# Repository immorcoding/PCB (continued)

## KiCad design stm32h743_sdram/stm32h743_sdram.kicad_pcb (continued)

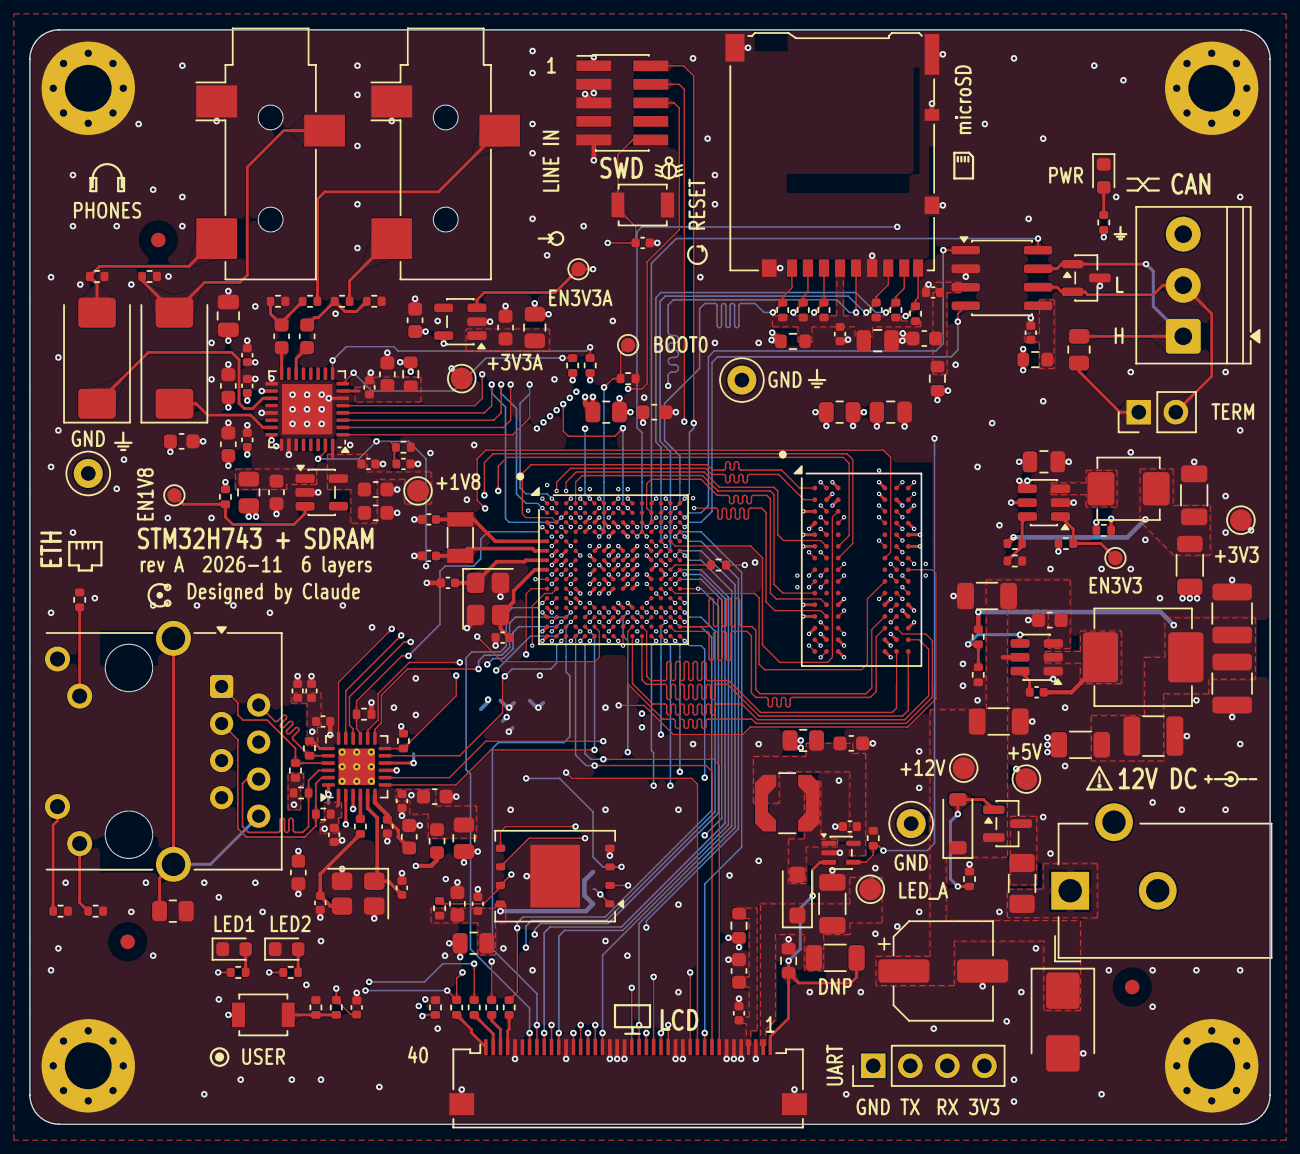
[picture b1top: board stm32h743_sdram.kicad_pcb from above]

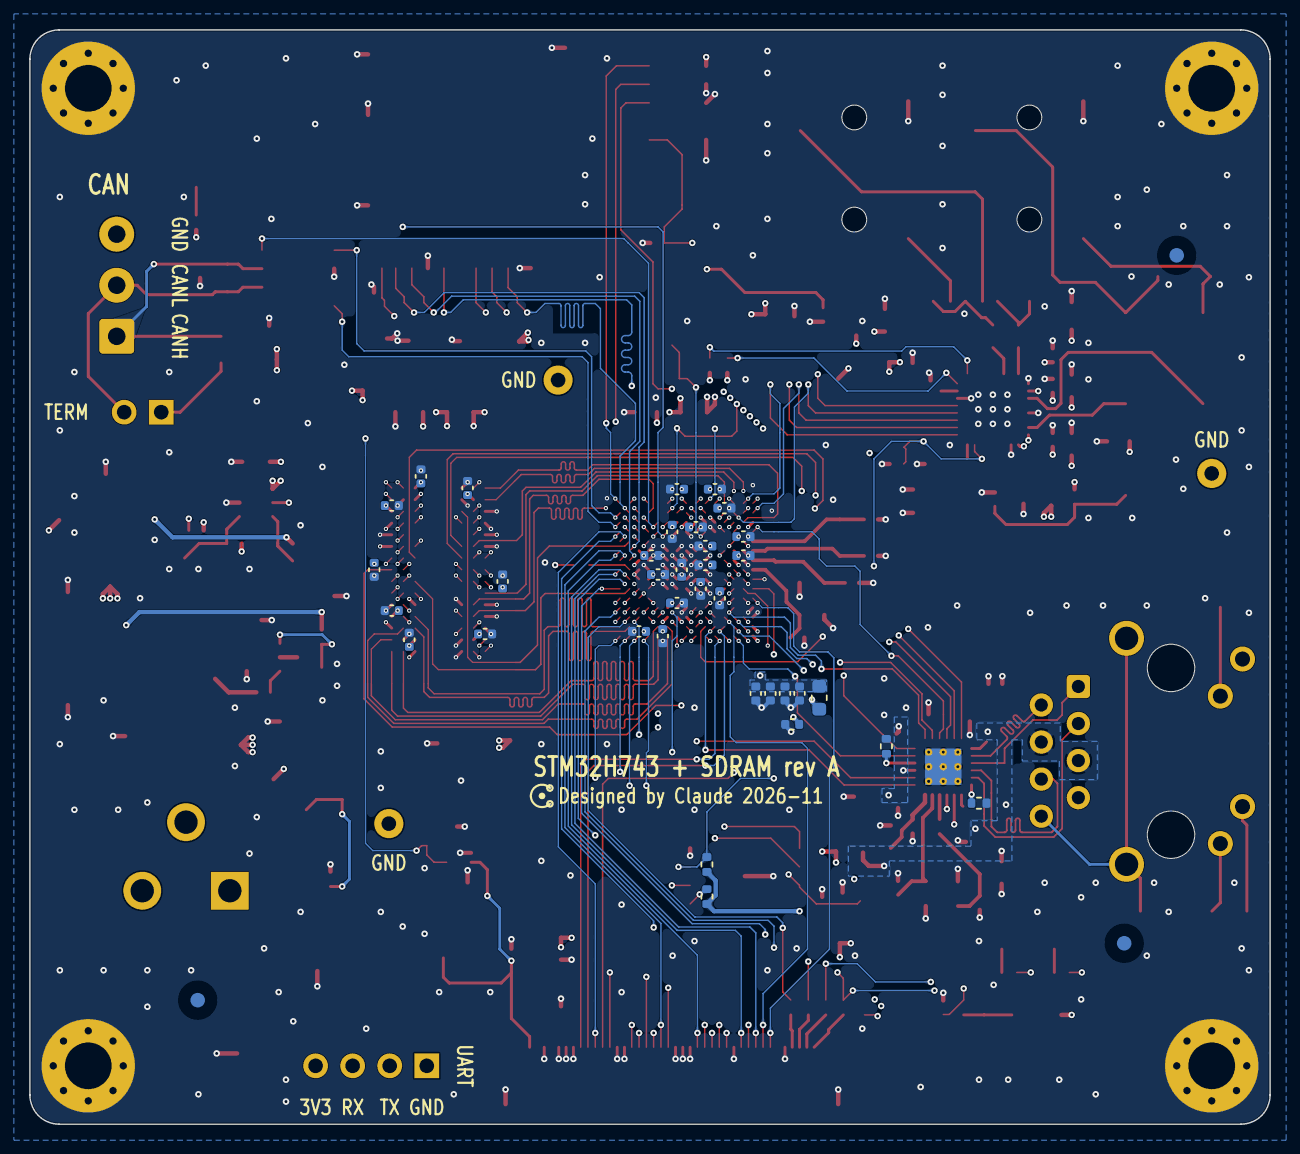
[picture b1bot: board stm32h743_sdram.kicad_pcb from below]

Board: 6 copper layers, 85.0 x 75.0 mm, 223 parts (38 on the bottom side), 204 nets.

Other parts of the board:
FID1, FID2, FID3, FID4, FID5, FID6: Fiducial; Fiducial_1mm_Mask2mm

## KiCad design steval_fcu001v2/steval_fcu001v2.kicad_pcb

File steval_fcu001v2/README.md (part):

# steval_fcu001v2

四层板 layout 测试：ST 官方评估板 STEVAL-FCU001V2（小四轴飞控）的原理图重新录入，加一块自己画的 40 × 40 mm 四层板。

- 原理图来源：`ref/steval-fcu001v2-schematic.pdf`（ST schematic pack Rev 2，2024-06），同目录有 BOM、data brief、UM2958。位号沿用 ST 的。
- 板子：嘉立创四层 JLC04161H-3313，1.6 mm，40 × 40 mm，四角 M3 孔。器件全在顶层，只有第二组电机焊盘在底层。
- 各层用途（2026-11-12 和用户定）：L1 信号和器件，L2 整层地，L3 电源层（`+BATT`，中间一块 `VDD`），L4 信号加铺地。

## 怎么重建

| 步骤 | 命令 |
|---|---|
| 原理图 | `D:\KiCad\bin\python.exe -m Tools.KiCadDesignTools.schematic.build steval_fcu001v2 <输出目录>` |
| 网表进板 | `D:\KiCad\bin\python.exe -m Tools.KiCadDesignTools.schematic.net2pcb <输出目录>\steval_fcu001v2.net steval_fcu001v2\steval_fcu001v2.kicad_pcb` |
| 整板（布局、走线、丝印、泪滴、DRC） | `sh steval_fcu001v2/build_pcb.sh <报告目录>` |

`route.py` 里是手工走线（按区域分函数）和铺铜；自动布线的 21 个网络存在 `auto_tracks.json` 里，由 `route.py` 回放。`auto_tracks.json` 已经用 `Tools/KiCadDesignTools/third_party/auto_tidy.py` 拉直过（过孔和分叉点不动，自动走线从最初的 387 段减到 217 段）；布线器绕远的路径没有改。重跑自动布线的做法见 `CLAUDE.md` 的"走线"一节。

## 审查清单

### 图

- `render_top.png`、`render_bottom.png`：3D 渲染。U1（蓝牙模块）官方库没有 3D 模型，图上只有丝印框。
- `routed.png`：走线示意图。
- 在 KiCad 里看：如果工程开着，先"文件 → 还原"重新载入。

### DRC（`analysis/drc.rpt`，带 `--schematic-parity`）

未连接 0。违规 22 条，逐条说明：

| 类型 | 数量 | 说明 |
|---|---|---|
| `track_angle` | 2（同一处报两次） | B.Cu 上 `MOTOR4` 在 (9.2, 11.7) 有一个 T 型抽头，接到不贴的 R19。是自动布线留下的；试过两种改法（改到过孔处），都会撞上旁边的 NRST，保留 |
| `starved_thermal` | 1 | P3 第 4 脚（GND 插针）在 F.Cu 铺铜上只有 1 根辐条。这个脚在 L2 地平面和 B.Cu 上辐条完整，不影响连接 |
| `silk_edge_clearance` | 5 | BT1（弯针伸出板边）和 CN1（USB 座伸出板边）的封装丝印越过板边，器件本来就悬出 |
| `silk_overlap` | 5 | LD1/LD2 两排 LED 的封装丝印框相碰（排距 1.6 mm），LD3 和 U4 的丝印相碰 |
| `lib_footprint_mismatch` | 9 | U7、U8、Q1–Q4 打开了"允许阻焊桥"，和库里的封装不一样了，原因见下面"规则改动"；P3、P6、P7 删掉了封装自带的丝印外框，原因见"丝印" |

封装一致性 102 条，全部是 `footprint_symbol_field_mismatch`（封装里没有符号的 `ki_keywords` 等字段，`net2pcb.py` 不复制这些字段），没有网络或焊盘不一致。

金丝雀：`OK`。

### 走线约定守得怎么样

| 约定 | 结果 |
|---|---|
| L2 整层地、L3 只做电源面 | 守住。L2、L3 上没有走线 |
| 晶振只走 L1、不打孔，下方 L4 不走线 | 守住。`OSC_IN` 8.2 mm、`OSC_OUT` 5.5 mm，B.Cu 上有禁布区 `XTAL_KEEPOUT` |
| USB 差分只走 L1，0.15/0.15 mm，对内差 ≤ 0.5 mm | 守住。MCU 侧 D+ 15.99 mm、D− 15.92 mm，差 0.07 mm。D+ 上有两个圆弧蛇形（半径 0.25 mm，摆幅 0.5 mm）用来补长。在 U3 处两根线绕开中间的地焊盘，分开 0.77 mm、长约 1.4 mm |
| 电机大电流走短粗线 | 守住。漏极到焊盘 1.0 mm / 0.8 mm 线宽，每个焊盘 3 个过孔连上下层；`+BATT` 走 L3 铜面 |
| 过孔 0.6 / 0.3 mm | **没守住**。MCU 引脚扇出等处用了 23 个 0.45 / 0.2 mm 过孔，其余 169 个是 0.6 / 0.3 |
| 信号线 0.2 mm | 大部分守住。834 mm 走线里 115 mm 是 0.15 mm：USB 差分、MCU 引脚到过孔的短线、蓝牙 SPI 五根线全程 |
| 不做盘中孔 | 两类例外：电机焊盘里的过孔（本来就是为了连上下层），复位键左侧接地焊盘里一个 0.45 mm 过孔（这个焊盘被 NRST、MOTOR3 和 LED 过孔围死）。另有 4 个过孔贴着同网络焊盘的边（C5.1、C19.1、C21.2、D5.2） |
| L4 少走信号 | 25 个网络上了 B.Cu，共 283 mm（F.Cu 是 551 mm）。MCU 四边的信号大多要换层才能出去 |

### 丝印（`silk.py`）

- **位号不上丝印**。按规则的最小字高 0.8 mm，102 个位号只有 55 个能找到不压焊盘的位置，所以一个都不印；位号仍在 F.Fab / B.Fab（AD 的 Assembly 层）上，装配图和贴片坐标不受影响。
- **只印功能标注**，字高 0.8 mm、字宽 0.6 mm、线宽 0.15 mm（`docs/design-rules.md` 的下限，没有再小）。共 52 条：正面 24 条、底面 20 条、电机焊盘正反各 4 条。
- **排针**：P3（I2C）、P6（TIM2）、P7（UART）是直插件，正反两面都标。底面每个引脚都有名字。正面 P7 和 P3 每个引脚都有名字（P3 的竖排在两排针之间）；P6 正面只标了两端的 `+` 和 `G`，中间四个引脚（TIM2 CH1–CH4，从 `+` 往 `G` 依次排）没有位置：排针塑料体到板边只剩 0.6 mm，和 P3 之间的空隙给了 P3 的引脚名。
- 为了放下引脚名，P3、P6、P7 封装自带的丝印外框删掉了，1 脚看方焊盘。
- 其余：`BAT` 和 `+`/`-`、`Mn+`（电机正极焊盘，另一个是负极）、`SWD`、`DIO`/`CLK`（TP1/TP2）、`RST`（按键和 TP3）、`CHG`（充电指示灯）、板名。LD1/LD2 两个用户灯没有标。
- **署名**（应用户要求）：底面蓝牙模块旁有一个四旋翼俯视图的小标志（4.5 mm 见方，自己画的）和三行字 `designed by` / `Claude` / `Fable 5.2 2026`，只在丝印层，压在走线和盖油过孔上，不压焊盘。

### 走线形状（`Tools/KiCadDesignTools/analysis/track_shape.py`，DRC 不查的部分）

2026-11-12 用户审查后返工过一轮，之后的结果：

| 项目 | 数量 | 说明 |
|---|---|---|
| 不在 0°/45°/90° 上的线段 | 0 | |
| 阶梯线（一串微小线段拼成的非 45° 斜线） | 0 | 返工前 `MOTOR1` 上有一段 22 级、2.6 mm 长、整体 78.5° 的阶梯 |
| 2 mm 内 3 个以上折弯 | 12 | 返工前 29 处。11 处在自动走线上，1 处是手工重走的 `MOTOR3` 绕按键焊盘的那一段（3 个折弯共 1.99 mm）。自动走线上的是两端过孔位置固定、中间要绕开焊盘或过孔造成的：`BLE_IRQ`、`LED1`、`LPS22HH_CS`、`MOTOR2`、`MOTOR3`（3 处）、`MOTOR4`、`NRST`（2 处）、`SWCLK`、`USB_MONITOR`、`VBAT_SENSE` |
| 短于 0.1 mm 的线段 | 0 | 返工前 32 个。现在由 DRC 规则 `min_segment` 兜底 |
| 小倒角直角（短于 0.35 mm 的线段两侧合计转 90°） | 0 | 2026-11-13 用户发现 `MOTOR3` 在 U2.45 下方有一处：两个 45° 拐点之间只隔 0.05 mm，相邻角度检查不报。同类共 4 处（`MOTOR3` 两处、`MOTOR1`、`S2_CLK`），都已重走；`MOTOR3` 从引脚直线下到自己的过孔，不再绕 `MOTOR2` 的过孔 |
| 圆弧 | 6 | USB D+ 的两个蛇形 |

### 走线过程中改过的规则

都写在 `steval_fcu001v2.kicad_dru` 开头和 `docs/design-rules.md`。

- **过孔下限 0.6/0.3 → 0.45/0.2 mm**：0.5 mm 间距的 QFN 引脚之间放不下 0.6 mm 过孔（相邻走线中心距 0.5 mm，0.6 过孔至少要 0.502 mm）。0.45/0.2 是嘉立创多层板的能力下限，下单时确认是否加价。
- **孔径下限 0.254 → 0.2、上限 3.048 → 3.3 mm**：前者配合小过孔，后者是 3.2 mm 安装孔。
- **`usb2_skew` 加 `within_diff_pairs`**：原写法把 MCU 侧的差分对（16 mm）和连接器侧的（2 mm）互相比较。
- **`usb2_gap` 上限 0.7 → 0.8 mm**：U3 处绕地焊盘分开的那一段是 0.77 mm。
- **网络类通配符**：`?` 和 `[+-]` 在 KiCad 的网络类匹配里不生效，改成逐个网络名。
- **U7、U8、Q1–Q4 允许阻焊桥**：0.5 mm 间距 LGA 焊盘和 MOS 管 0.65 mm 间距的源/栅焊盘之间，阻焊桥只有 0.05 mm，低于 0.08 mm 下限，板厂会整组开窗。不打开这个选项会报 28 条 `solder_mask_bridge`。

### 走线过程中改过的布局

- LED 挪了两次：先从 MCU 左侧挪走（挡住 USB 差分在 L1 上唯一的通道），再从 MCU 正下方下移（给引脚扇出过孔让位）。
- 晶振下移 1.35 mm，让 `OSC_OUT` 直线进晶振，不挡 NRST 等引脚出线。
- C5、C7、C11、R22、C10、C14、C15、R30 各挪了 0.3–1 mm，都是为过孔或走线通道让位；C10 转了 180°。
- 充电的阻容一列（R30、C15、C14）上移 1.05 mm，USB 差分才能在它下方横移到 U3。

### kicad-happy 的发现（`analysis/kicad_happy_*.txt`）

| 发现 | 判断 |
|---|---|
| 没有光学定位点（FD-001） | 属实。机贴需要，每面 3 个；手焊打样不需要。板上没留位置，要加得再挤 |
| 15 个信号网络最细 0.15 mm（CC-002） | 属实但无碍：数字信号的引脚逃逸段 |
| 测试点覆盖 3/72（TE-001） | 属实，ST 原设计就只有 3 个 |
| `S2_SDI`/`S2_CLK` 是 I2C、缺上拉（PR-001） | 误报。这是 SPI，符号的引脚名叫 SDA/SCL |
| U4 的 STAT 缺上拉（PU-001） | 误报。STAT 经 LD3 和 R29 接 VBUS |
| `USBLC_VBUS` 没有电源（RS-001） | ST 原图如此：U3 的 VBUS 脚只接一个电容 |
| BOM 没有料号、没有规格书（SS-001、DS-001） | 属实，见"未核对项" |

## 和 ST 图纸不一样的地方

| ST 图纸 | 这里 | 原因 |
|---|---|---|
| `V_USB`、`VBAT+` | `VBUS`、`+BATT` | 用 KiCad 自带电源符号 |
| `USB_DP` / `USB_DM`（MCU 侧） | `USB_D+` / `USB_D-` | KiCad 靠 `+`/`-` 后缀识别差分对 |
| `DP` / `DM`（连接器侧） | `USB_CONN_D+` / `USB_CONN_D-` | 同上 |
| `MOTORn-` | `MOTORn_N` | 避免被当成差分对的负端 |
| R25（0R，接在两种地符号之间） | 去掉，只有一个 `GND` | 四层板有完整地平面 |
| 电机排针 P1 / P4 / P2 / P5（2 针） | 裸焊盘 MP1–MP16（每个电机 `+BATT` 和 `Mn_OUT` 各一个，1.5 × 3 mm；MP1–8 在顶层，MP9–16 在底层同一位置） | 用户要求 |
| CN1 Molex 47590-0001（micro-AB，沉板，板边要开槽） | Molex 47346-0001（micro-B，贴片，直板边） | 不开槽；引脚顺序相反，USB 差分对从 MCU 到座子不用交叉 |
| 没有安装孔 | H1–H4，M3 | 原型板固定用 |
| 栅极、LED 阳极等没有名字的节点 | `Mn_GATE`、`LDn_A`、`Mn_OUT`、`CHG_PROG`、`CHG_STAT`、`USB_SHIELD`、`USBLC_VBUS` | 标号画法需要名字 |

## 符号和封装的替代

官方库里没有的器件，用引脚号相同的符号顶替，Value 写的是 ST 的型号。

| 位号 | ST 型号 | 用的符号 | 用的封装 |
|---|---|---|---|
| U3 | USBULC6-2M6（µQFN 1.45×1.0） | `USBLC6-2P6` | `Texas_USON-6_1x1.45mm_P0.5mm_SMD` |
| U4 | STC4054GR（TSOT23-5） | `MCP73831-2-OT` | `TSOT-23-5` |
| U8 | LSM6DSR（LGA-14） | `LSM6DSL` | `LGA-14_3x2.5mm_P0.5mm_LayoutBorder3x4y` |
| U1 | BLUENRG-M0A | `SPBTLE-RF` | `ST_SPBTLE` |
| Q1–Q4 | STL10N3LLH5（图纸）/ STL6N3LLH6（BOM） | `Q_NMOS_SSSGD` | `VSON-8_3.3x3.3mm_P0.65mm_NexFET` |
| D5 | ESDA7P60-1U1M | `D_Zener` | `ST_QFN-2L_1.6x1.0mm` |

## 未核对项

没有对着规格书核对过的引脚、封装和参数。

1. **Q1–Q4 型号和封装**：ST 图纸写 STL10N3LLH5（8 脚，1–3 源极、4 栅极、5–8 漏极），BOM 写 STL6N3LLH6（PowerFLAT 2×2）。这里按图纸的引脚功能，封装用了 3.3×3.3 的通用 VSON-8，没核对过 ST 的推荐焊盘。
2. **U3 封装**：用了尺寸相同的 TI USON-6 顶替，焊盘编号顺序和尺寸没对过 USBULC6-2M6 规格书。
3. **U1 封装和天线净空**：假定 BLUENRG-M0A 和 SPBTLE-RF 焊盘相同。`ST_SPBTLE` 封装自带 12 × 12 mm 的四层禁布区，布局和走线都避开了；这个尺寸是 SPBTLE-RF 的。蓝牙 SPI 五根线从模块下方（禁布区外）的 L1 走，模块底面是否允许走线没查。
4. **U4 引脚**：按图纸上的引脚号（1 CHRG、2 GND、3 BAT、4 VCC、5 PROG）录入，没对过 STC4054 规格书。
5. **U8 引脚**：LSM6DSR 借用 LSM6DSL 符号，图纸上的引脚号和符号一致，没对过规格书。
6. **S1**：KMR231GLFS 用了带接地脚的 `KMR2xxG` 封装，接地脚接 GND；型号是否带接地脚没查。
7. **D5 极性**：按图纸 1 脚接 VBUS；封装的 1 号焊盘是否是阴极没查。
8. **Y1**：BOM 里晶振的型号没读出来（PDF 表格文字错位），封装暂用 3225 四脚，负载电容 15 pF 沿用图纸。
9. **排针**：BT1 用 2.54 mm 弯针，P3、P7、P6 用直针，P8 用 1.27 mm 2×5 贴片针；BOM 的具体料号没逐个对封装。
10. **阻容封装**：统一 0402（图纸上 R1 标 0805、R26 标 0201，BOM 都是 0402）；R12、R13、R16、R17 按 BOM 用 0603。
11. **原板尺寸和外形**：没查。V1 的 Gerber 是双层板，没有官方四层 layout 可对照。
12. **叠层数据**：3313 半固化片 0.0994 mm / Er 4.1、芯板 1.265 mm 是凭记忆写的，没在嘉立创阻抗计算器上核对。USB 线宽 0.15 / 间距 0.15 mm 是按 IPC-2141 公式估的（约 88 Ω）；这块板的 USB 只有全速。
13. **CN1 板边位置**：板边放在封装原点下方 2.7 mm（外壳焊盘外 0.55 mm），没对过 Molex 47346-0001 图纸上的板边尺寸。
14. **0.45/0.2 mm 过孔的价格档**：是否在嘉立创四层板的免加价范围内没查。
15. **L3 上 `+BATT` 的通流**：L3 的 `+BATT` 是围着 `VDD` 岛的一圈，上边在蓝牙天线禁布区下方只有约 2.6 mm 宽（0.5 oz 铜）。四个电机同时峰值电流时的压降和温升没算。

## ERC

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
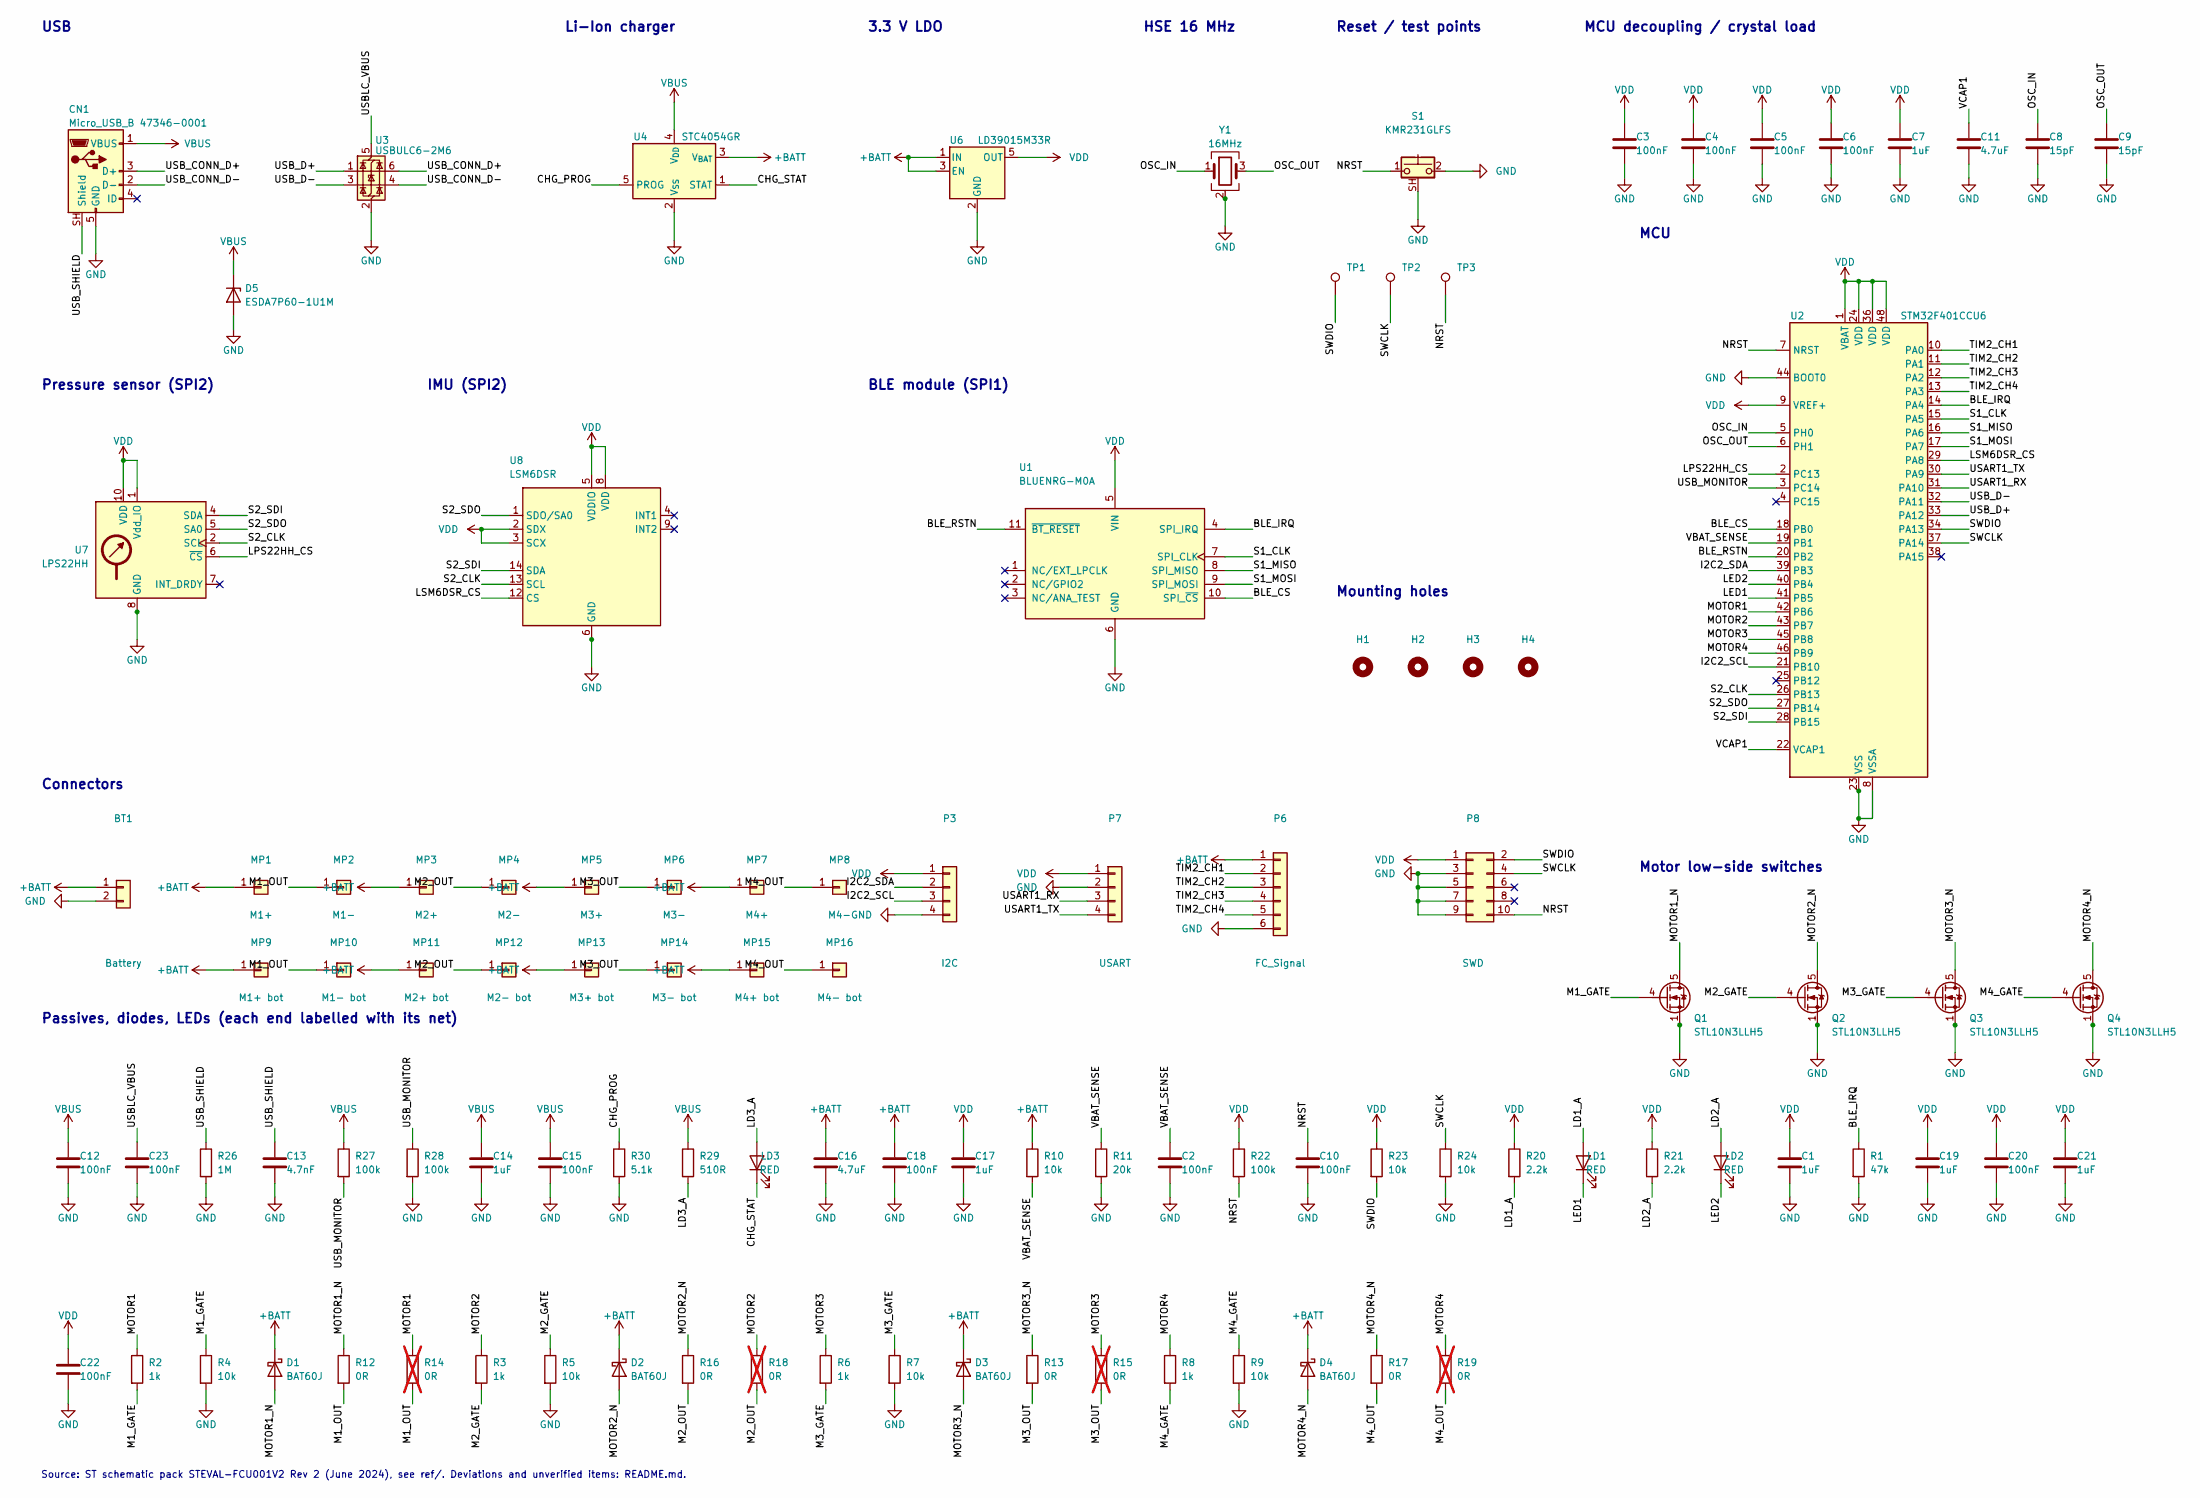
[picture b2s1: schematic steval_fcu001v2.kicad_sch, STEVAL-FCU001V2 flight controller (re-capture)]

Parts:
BT1: Battery; PinHeader_1x02_P2.54mm_Horizontal
C1, C7, C14, C17, C19, C21: 1uF; C_0402_1005Metric
C2, C3, C4, C5, C6, C10, C12, C15, C18, C20, C22, C23: 100nF; C_0402_1005Metric
C8, C9: 15pF; C_0402_1005Metric
C11, C16: 4.7uF; C_0402_1005Metric
C13: 4.7nF; C_0402_1005Metric
CN1: Micro_USB_B 47346-0001; USB_Micro-B_Molex_47346-0001
D1, D2, D3, D4: BAT60J; D_SOD-323
D5: ESDA7P60-1U1M; ST_QFN-2L_1.6x1.0mm
H1, H2, H3, H4: M3; MountingHole_3.2mm_M3
LD1, LD2, LD3: RED; LED_0603_1608Metric
MP1: M1+; SolderWirePad_1x01_SMD_1.5x3mm
MP2: M1-; SolderWirePad_1x01_SMD_1.5x3mm
MP3: M2+; SolderWirePad_1x01_SMD_1.5x3mm
MP4: M2-; SolderWirePad_1x01_SMD_1.5x3mm
MP5: M3+; SolderWirePad_1x01_SMD_1.5x3mm
MP6: M3-; SolderWirePad_1x01_SMD_1.5x3mm
MP7: M4+; SolderWirePad_1x01_SMD_1.5x3mm
MP8: M4-; SolderWirePad_1x01_SMD_1.5x3mm
MP9: M1+ bot; SolderWirePad_1x01_SMD_1.5x3mm
MP10: M1- bot; SolderWirePad_1x01_SMD_1.5x3mm
MP11: M2+ bot; SolderWirePad_1x01_SMD_1.5x3mm
MP12: M2- bot; SolderWirePad_1x01_SMD_1.5x3mm
MP13: M3+ bot; SolderWirePad_1x01_SMD_1.5x3mm
MP14: M3- bot; SolderWirePad_1x01_SMD_1.5x3mm
MP15: M4+ bot; SolderWirePad_1x01_SMD_1.5x3mm
MP16: M4- bot; SolderWirePad_1x01_SMD_1.5x3mm
P3: I2C; PinHeader_1x04_P2.54mm_Vertical
P6: FC_Signal; PinHeader_1x06_P2.54mm_Vertical
P7: USART; PinHeader_1x04_P2.54mm_Vertical
P8: SWD; PinHeader_2x05_P1.27mm_Vertical_SMD
Q1, Q2, Q3, Q4: STL10N3LLH5; VSON-8_3.3x3.3mm_P0.65mm_NexFET
R1: 47k; R_0402_1005Metric
R2, R3, R6, R8: 1k; R_0402_1005Metric
R4, R5, R7, R9, R10, R23, R24: 10k; R_0402_1005Metric
R11: 20k; R_0402_1005Metric
R12, R13, R16, R17: 0R; R_0603_1608Metric
R14, R15, R18, R19: 0R; R_0402_1005Metric; not fitted
R20, R21: 2.2k; R_0402_1005Metric
R22, R27, R28: 100k; R_0402_1005Metric
R26: 1M; R_0402_1005Metric
R29: 510R; R_0402_1005Metric
R30: 5.1k; R_0402_1005Metric
S1: KMR231GLFS; SW_Push_1P1T-SH_NO_CK_KMR2xxG
TP1, TP2, TP3: TP; TestPoint_Pad_D1.0mm
U1: BLUENRG-M0A; ST_SPBTLE
U2: STM32F401CCU6; QFN-48-1EP_7x7mm_P0.5mm_EP5.6x5.6mm
U3: USBULC6-2M6; Texas_USON-6_1x1.45mm_P0.5mm_SMD
U4: STC4054GR; TSOT-23-5
U6: LD39015M33R; SOT-23-5
U7: LPS22HH; ST_HLGA-10_2x2mm_P0.5mm_LayoutBorder3x2y
U8: LSM6DSR; LGA-14_3x2.5mm_P0.5mm_LayoutBorder3x4y
Y1: 16MHz; Crystal_SMD_3225-4Pin_3.2x2.5mm

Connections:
+BATT: BT1.1, C16.1, C18.1, D1.1 (K), D2.1 (K), D3.1 (K), D4.1 (K), MP1.1, MP3.1, MP5.1, MP7.1, MP9.1, MP11.1, MP13.1, MP15.1, P6.1, R10.1, U4.3 (V_{BAT}), U6.1 (IN), U6.3 (EN)
/BLE_CS: U1.10 (SPI_~CS), U2.18 (PB0)
/BLE_IRQ: R1.1, U1.4 (SPI_IRQ), U2.14 (PA4)
/BLE_RSTN: U1.11 (~BT_RESET), U2.20 (PB2)
/CHG_PROG: R30.1, U4.5 (PROG)
/CHG_STAT: LD3.1 (K), U4.1 (STAT)
/I2C2_SCL: P3.3, U2.21 (PB10)
/I2C2_SDA: P3.2, U2.39 (PB3)
/LD1_A: LD1.2 (A), R20.2
/LD2_A: LD2.2 (A), R21.2
/LD3_A: LD3.2 (A), R29.2
/LED1: LD1.1 (K), U2.41 (PB5)
/LED2: LD2.1 (K), U2.40 (PB4)
/LPS22HH_CS: U2.2 (PC13), U7.6 (~CS)
/LSM6DSR_CS: U2.29 (PA8), U8.12 (CS)
/M1_GATE: Q1.4 (G), R2.2, R4.1
/M1_OUT: MP2.1, MP10.1, R12.2, R14.2
/M2_GATE: Q2.4 (G), R3.2, R5.1
/M2_OUT: MP4.1, MP12.1, R16.2, R18.2
/M3_GATE: Q3.4 (G), R6.2, R7.1
/M3_OUT: MP6.1, MP14.1, R13.2, R15.2
/M4_GATE: Q4.4 (G), R8.2, R9.1
/M4_OUT: MP8.1, MP16.1, R17.2, R19.2
/MOTOR1: R2.1, R14.1, U2.42 (PB6)
/MOTOR1_N: D1.2 (A), Q1.5 (D), R12.1
/MOTOR2: R3.1, R18.1, U2.43 (PB7)
/MOTOR2_N: D2.2 (A), Q2.5 (D), R16.1
/MOTOR3: R6.1, R15.1, U2.45 (PB8)
/MOTOR3_N: D3.2 (A), Q3.5 (D), R13.1
/MOTOR4: R8.1, R19.1, U2.46 (PB9)
/MOTOR4_N: D4.2 (A), Q4.5 (D), R17.1
/NRST: C10.1, P8.10, R22.2, S1.1, TP3.1, U2.7 (NRST)
/OSC_IN: C8.1, U2.5 (PH0), Y1.1
/OSC_OUT: C9.1, U2.6 (PH1), Y1.3
/S1_CLK: U1.7 (SPI_CLK), U2.15 (PA5)
/S1_MISO: U1.8 (SPI_MISO), U2.16 (PA6)
/S1_MOSI: U1.9 (SPI_MOSI), U2.17 (PA7)
/S2_CLK: U2.26 (PB13), U7.2 (SCL), U8.13 (SCL)
/S2_SDI: U2.28 (PB15), U7.4 (SDA), U8.14 (SDA)
/S2_SDO: U2.27 (PB14), U7.5 (SA0), U8.1 (SDO/SA0)
/SWCLK: P8.4, R24.1, TP2.1, U2.37 (PA14)
/SWDIO: P8.2, R23.2, TP1.1, U2.34 (PA13)
/TIM2_CH1: P6.2, U2.10 (PA0)
/TIM2_CH2: P6.3, U2.11 (PA1)
/TIM2_CH3: P6.4, U2.12 (PA2)
/TIM2_CH4: P6.5, U2.13 (PA3)
/USART1_RX: P7.3, U2.31 (PA10)
/USART1_TX: P7.4, U2.30 (PA9)
/USBLC_VBUS: C23.1, U3.5 (VBUS)
/USB_CONN_D+: CN1.3 (D+), U3.6 (I/O1)
/USB_CONN_D-: CN1.2 (D-), U3.4 (I/O2)
/USB_D+: U2.33 (PA12), U3.1 (I/O1)
/USB_D-: U2.32 (PA11), U3.3 (I/O2)
/USB_MONITOR: R27.2, R28.1, U2.3 (PC14)
/USB_SHIELD: C13.1, CN1.SH (Shield), R26.1
/VBAT_SENSE: C2.1, R10.2, R11.1, U2.19 (PB1)
/VCAP1: C11.1, U2.22 (VCAP1)
GND: BT1.2, C1.2, C2.2, C3.2, C4.2, C5.2, C6.2, C7.2, C8.2, C9.2, C10.2, C11.2, C12.2, C13.2, C14.2, C15.2, C16.2, C17.2, C18.2, C19.2, C20.2, C21.2, C22.2, C23.2, CN1.5 (GND), D5.2 (A), P3.4, P6.6, P7.2, P8.3, P8.5, P8.7, P8.9, Q1.1 (S), Q1.2 (S), Q1.3 (S), Q2.1 (S), Q2.2 (S), Q2.3 (S), Q3.1 (S), Q3.2 (S), Q3.3 (S), Q4.1 (S), Q4.2 (S), Q4.3 (S), R1.2, R4.2, R5.2, R7.2, R9.2, R11.2, R24.2, R26.2, R28.2, R30.2, S1.2, S1.SH (B), U1.6 (GND), U2.8 (VSSA), U2.23 (VSS), U2.35 (VSS), U2.44 (BOOT0), U2.47 (VSS), U2.49 (VSS), U3.2 (GND), U4.2 (V_{SS}), U6.2 (GND), U7.3 (GND), U7.8 (GND), U7.9 (GND), U8.6 (GND), U8.7 (GND), Y1.2 (G), Y1.4 (G)
VBUS: C12.1, C14.1, C15.1, CN1.1 (VBUS), D5.1 (K), R27.1, R29.1, U4.4 (V_{DD})
VDD: C1.1, C3.1, C4.1, C5.1, C6.1, C7.1, C17.1, C19.1, C20.1, C21.1, C22.1, P3.1, P7.1, P8.1, R20.1, R21.1, R22.1, R23.1, U1.5 (VIN), U2.1 (VBAT), U2.9 (VREF+), U2.24 (VDD), U2.36 (VDD), U2.48 (VDD), U6.5 (OUT), U7.1 (Vdd_IO), U7.10 (VDD), U8.2 (SDX), U8.3 (SCX), U8.5 (VDDIO), U8.8 (VDD)

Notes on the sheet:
Mounting holes
MCU decoupling / crystal load
3.3 V LDO
IMU (SPI2)
Passives, diodes, LEDs (each end labelled with its net)
Motor low-side switches
Li-Ion charger
MCU
Pressure sensor (SPI2)
BLE module (SPI1)
USB
Source: ST schematic pack STEVAL-FCU001V2 Rev 2 (June 2024), see ref/. Deviations and unverified items: README.md.
Connectors
HSE 16 MHz
Reset / test points

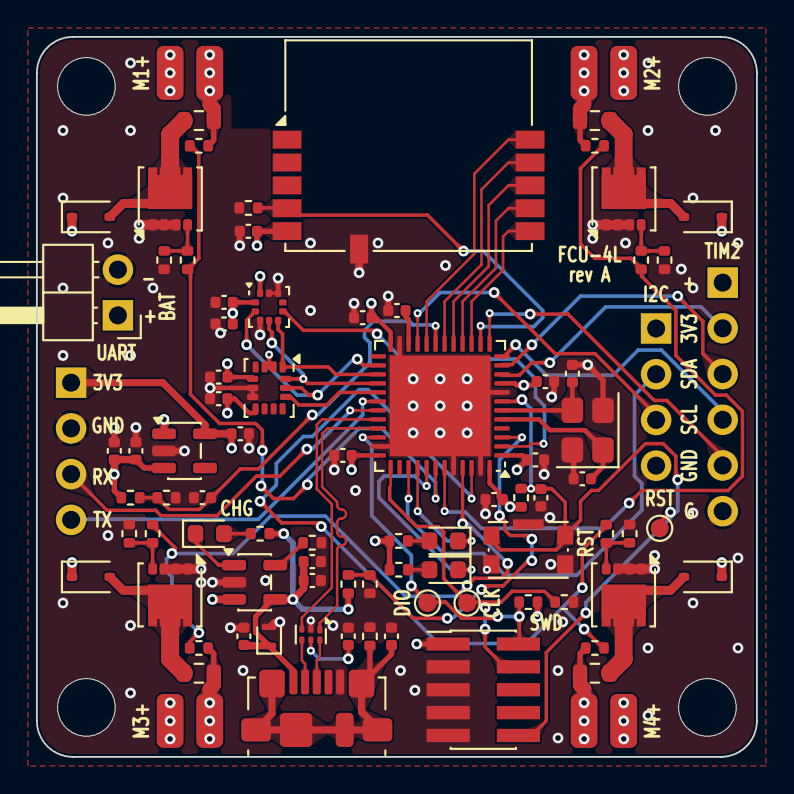
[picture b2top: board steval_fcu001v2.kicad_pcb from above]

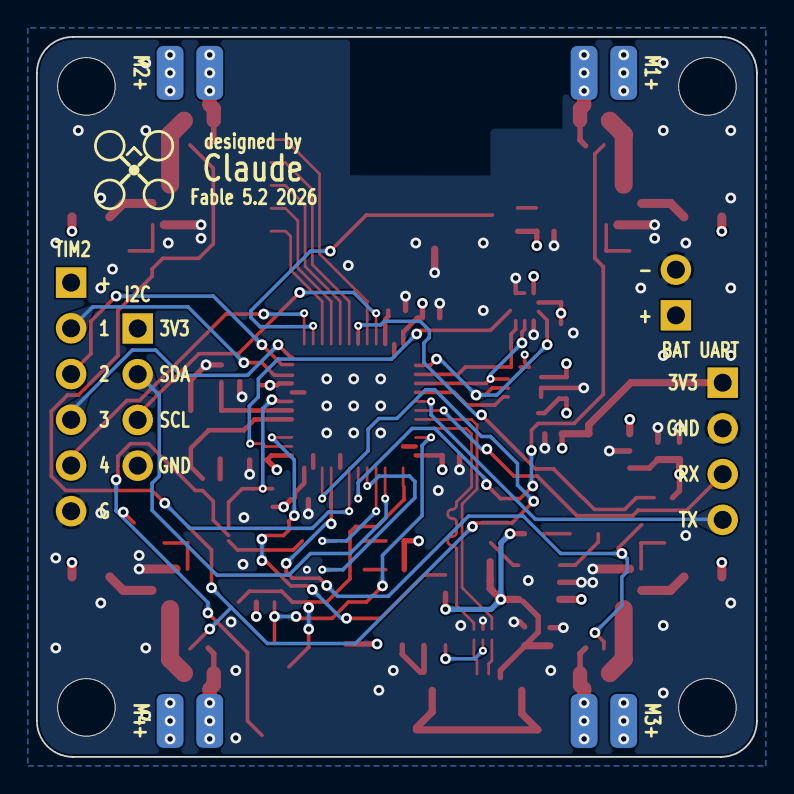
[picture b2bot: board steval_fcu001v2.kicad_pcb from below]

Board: 4 copper layers, 40.0 x 40.0 mm, 102 parts (8 on the bottom side), 60 nets.

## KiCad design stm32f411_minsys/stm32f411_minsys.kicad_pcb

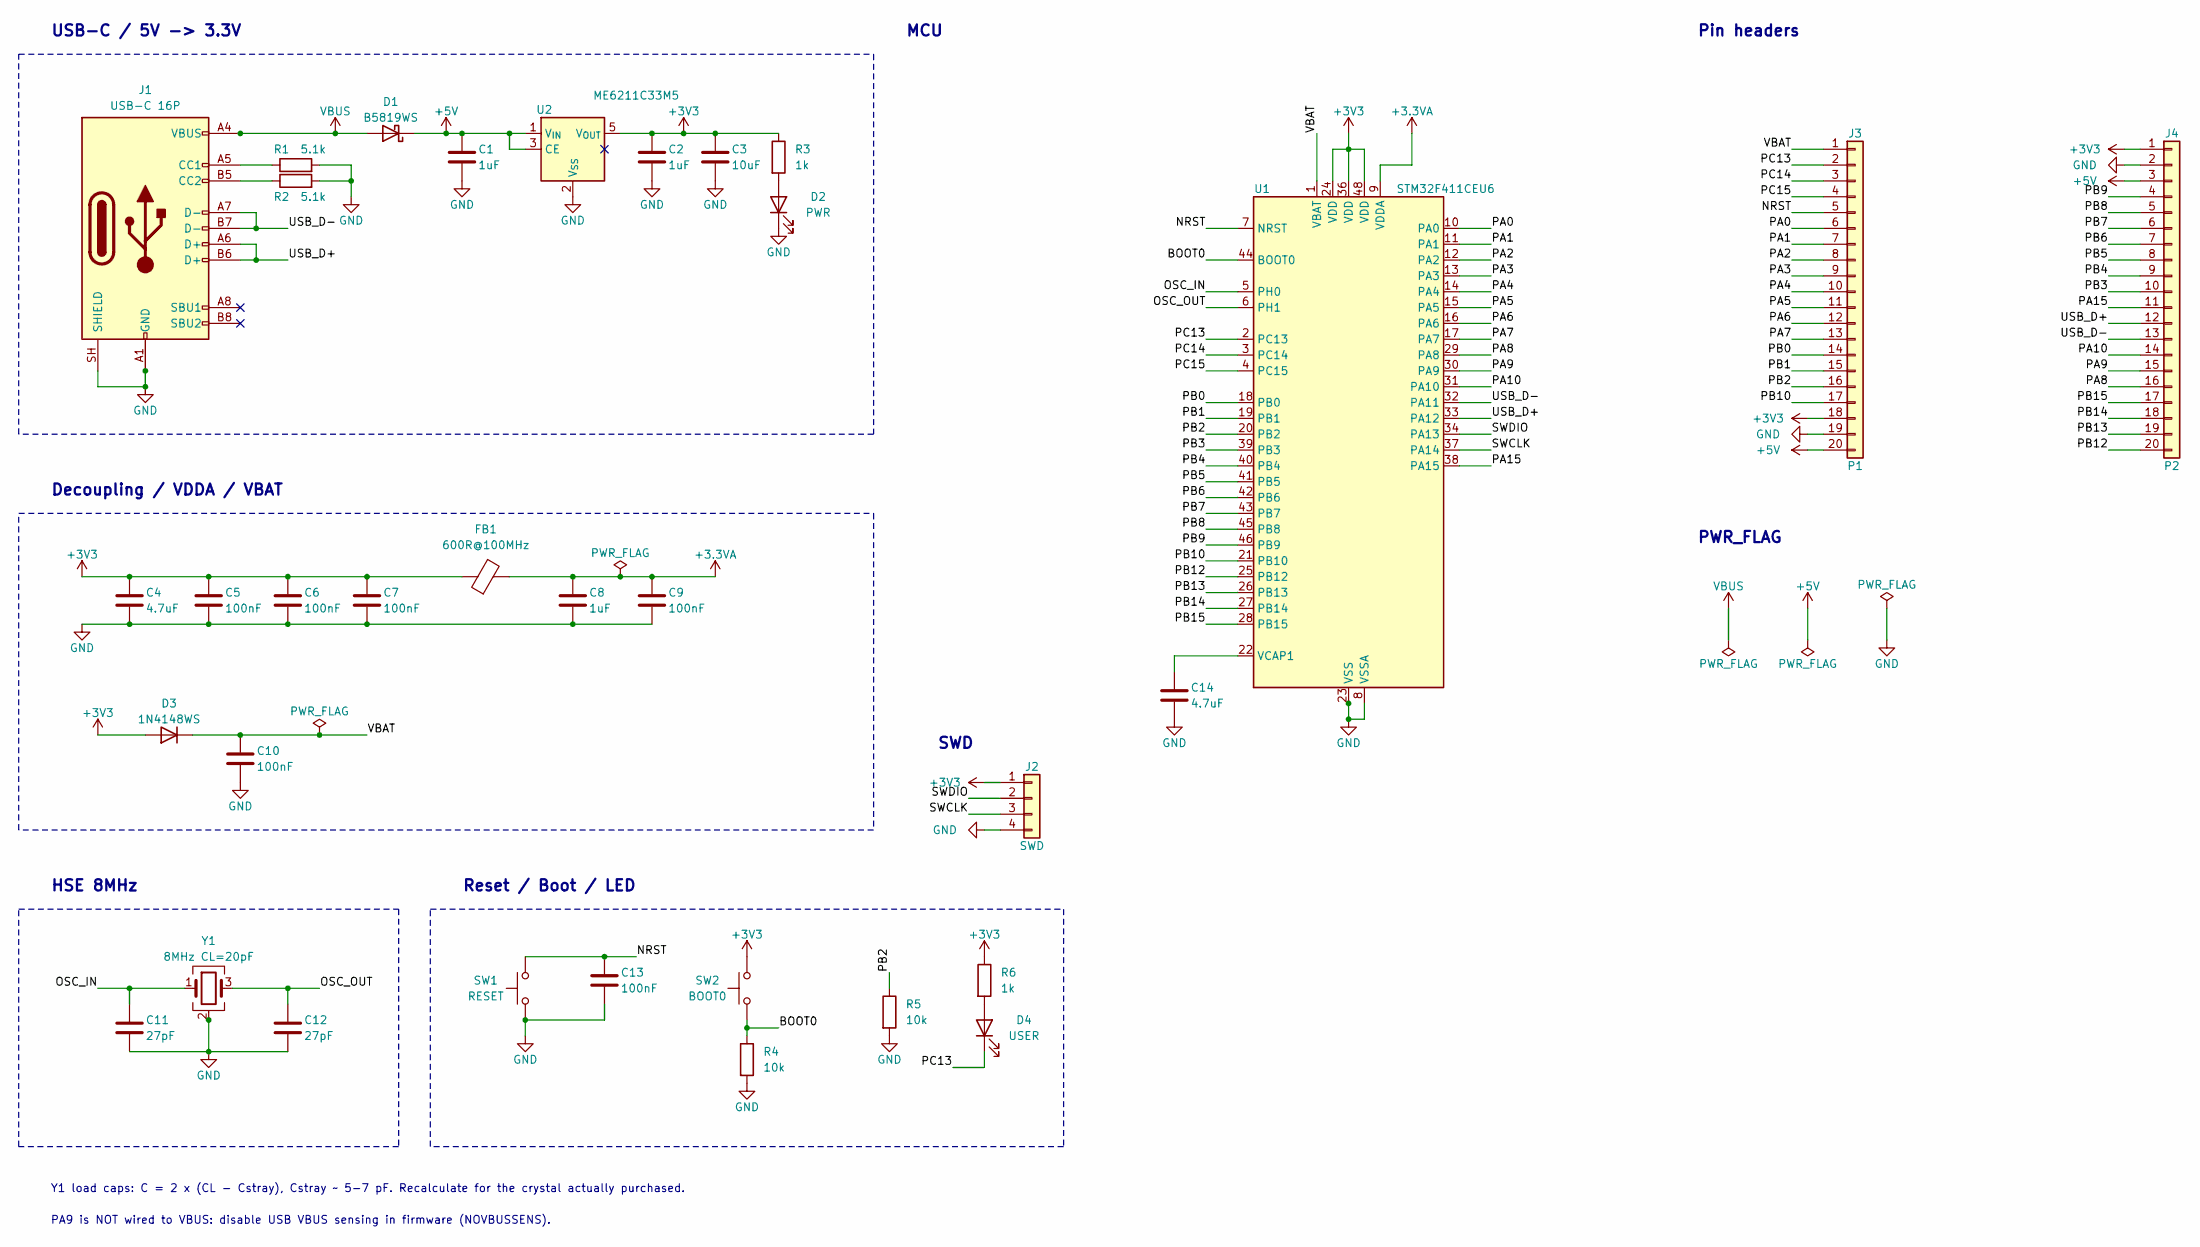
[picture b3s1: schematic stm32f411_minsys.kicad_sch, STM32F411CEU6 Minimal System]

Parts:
C1, C2, C8: 1uF; C_0603_1608Metric
C3: 10uF; C_0603_1608Metric
C4, C14: 4.7uF; C_0603_1608Metric
C5, C6, C7, C9, C10, C13: 100nF; C_0603_1608Metric
C11, C12: 27pF; C_0603_1608Metric
D1: B5819WS; D_SOD-323
D2: PWR; LED_0603_1608Metric
D3: 1N4148WS; D_SOD-323
D4: USER; LED_0603_1608Metric
FB1: 600R@100MHz; L_0603_1608Metric
J1: USB-C 16P; USB_C_Receptacle_HRO_TYPE-C-31-M-12
J2: SWD; PinHeader_1x04_P2.54mm_Horizontal
J3: P1; PinHeader_1x20_P2.54mm_Vertical
J4: P2; PinHeader_1x20_P2.54mm_Vertical
R1, R2: 5.1k; R_0603_1608Metric
R3, R6: 1k; R_0603_1608Metric
R4, R5: 10k; R_0603_1608Metric
SW1: RESET; SW_SPST_TS-1088-xR020
SW2: BOOT0; SW_SPST_TS-1088-xR020
U1: STM32F411CEU6; QFN-48-1EP_7x7mm_P0.5mm_EP5.6x5.6mm
U2: ME6211C33M5; SOT-23-5
Y1: 8MHz CL=20pF; Crystal_SMD_3225-4Pin_3.2x2.5mm

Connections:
+3.3VA: C8.1, C9.1, FB1.2, U1.9 (VDDA)
+3V3: C2.1, C3.1, C4.1, C5.1, C6.1, C7.1, D3.2 (A), FB1.1, J2.1, J3.18, J4.1, R3.1, R6.1, SW2.2, U1.24 (VDD), U1.36 (VDD), U1.48 (VDD), U2.5 (V_{OUT})
+5V: C1.1, D1.1 (K), J3.20, J4.3, U2.1 (V_{IN}), U2.3 (CE)
/BOOT0: R4.1, SW2.1, U1.44 (BOOT0)
/NRST: C13.1, J3.5, SW1.2, U1.7 (NRST)
/OSC_IN: C11.1, U1.5 (PH0), Y1.1
/OSC_OUT: C12.1, U1.6 (PH1), Y1.3
/PA0: J3.6, U1.10 (PA0)
/PA1: J3.7, U1.11 (PA1)
/PA2: J3.8, U1.12 (PA2)
/PA3: J3.9, U1.13 (PA3)
/PA4: J3.10, U1.14 (PA4)
/PA5: J3.11, U1.15 (PA5)
/PA6: J3.12, U1.16 (PA6)
/PA7: J3.13, U1.17 (PA7)
/PA8: J4.16, U1.29 (PA8)
/PA9: J4.15, U1.30 (PA9)
/PA10: J4.14, U1.31 (PA10)
/PA15: J4.11, U1.38 (PA15)
/PB0: J3.14, U1.18 (PB0)
/PB1: J3.15, U1.19 (PB1)
/PB2: J3.16, R5.1, U1.20 (PB2)
/PB3: J4.10, U1.39 (PB3)
/PB4: J4.9, U1.40 (PB4)
/PB5: J4.8, U1.41 (PB5)
/PB6: J4.7, U1.42 (PB6)
/PB7: J4.6, U1.43 (PB7)
/PB8: J4.5, U1.45 (PB8)
/PB9: J4.4, U1.46 (PB9)
/PB10: J3.17, U1.21 (PB10)
/PB12: J4.20, U1.25 (PB12)
/PB13: J4.19, U1.26 (PB13)
/PB14: J4.18, U1.27 (PB14)
/PB15: J4.17, U1.28 (PB15)
/PC13: D4.1 (K), J3.2, U1.2 (PC13)
/PC14: J3.3, U1.3 (PC14)
/PC15: J3.4, U1.4 (PC15)
/SWCLK: J2.3, U1.37 (PA14)
/SWDIO: J2.2, U1.34 (PA13)
/USB_D+: J1.A6 (D+), J1.B6 (D+), J4.12, U1.33 (PA12)
/USB_D-: J1.A7 (D-), J1.B7 (D-), J4.13, U1.32 (PA11)
/VBAT: C10.1, D3.1 (K), J3.1, U1.1 (VBAT)
GND: C1.2, C2.2, C3.2, C4.2, C5.2, C6.2, C7.2, C8.2, C9.2, C10.2, C11.2, C12.2, C13.2, C14.2, D2.1 (K), J1.A1 (GND), J1.A12 (GND), J1.B1 (GND), J1.B12 (GND), J1.SH (SHIELD), J2.4, J3.19, J4.2, R1.2, R2.2, R4.2, R5.2, SW1.1, U1.8 (VSSA), U1.23 (VSS), U1.35 (VSS), U1.47 (VSS), U1.49 (VSS), U2.2 (V_{SS}), Y1.2 (G), Y1.4 (G)
unnamed: D2.2 (A), R3.2
unnamed: D4.2 (A), R6.2
unnamed: J1.A5 (CC1), R1.1
unnamed: J1.B5 (CC2), R2.1
unnamed: C14.1, U1.22 (VCAP1)
VBUS: D1.2 (A), J1.A4 (VBUS), J1.A9 (VBUS), J1.B4 (VBUS), J1.B9 (VBUS)

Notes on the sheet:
PA9 is NOT wired to VBUS: disable USB VBUS sensing in firmware (NOVBUSSENS).
MCU
HSE 8MHz
PWR_FLAG
Reset / Boot / LED
Decoupling / VDDA / VBAT
SWD
Y1 load caps: C = 2 x (CL - Cstray), Cstray ~ 5-7 pF. Recalculate for the crystal actually purchased.
USB-C / 5V -> 3.3V
Pin headers

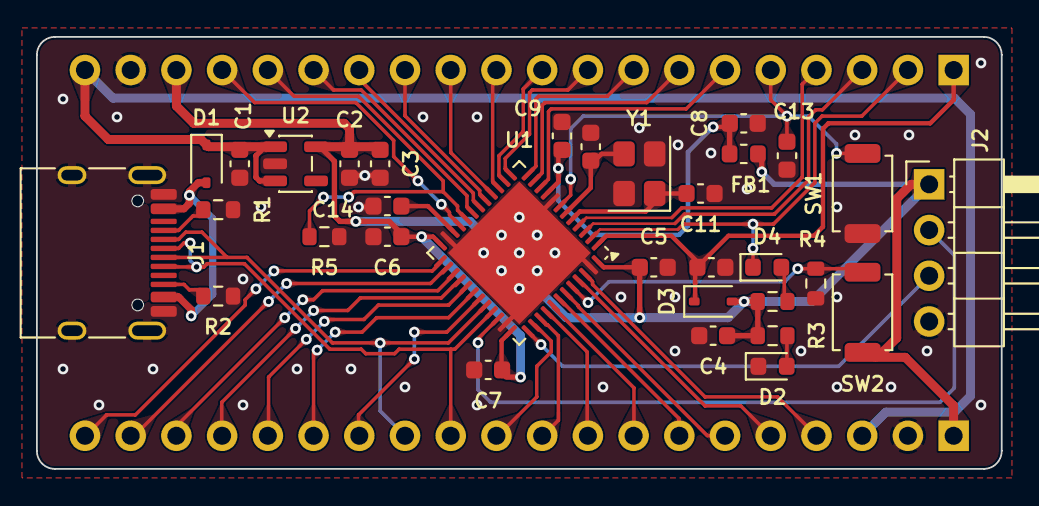
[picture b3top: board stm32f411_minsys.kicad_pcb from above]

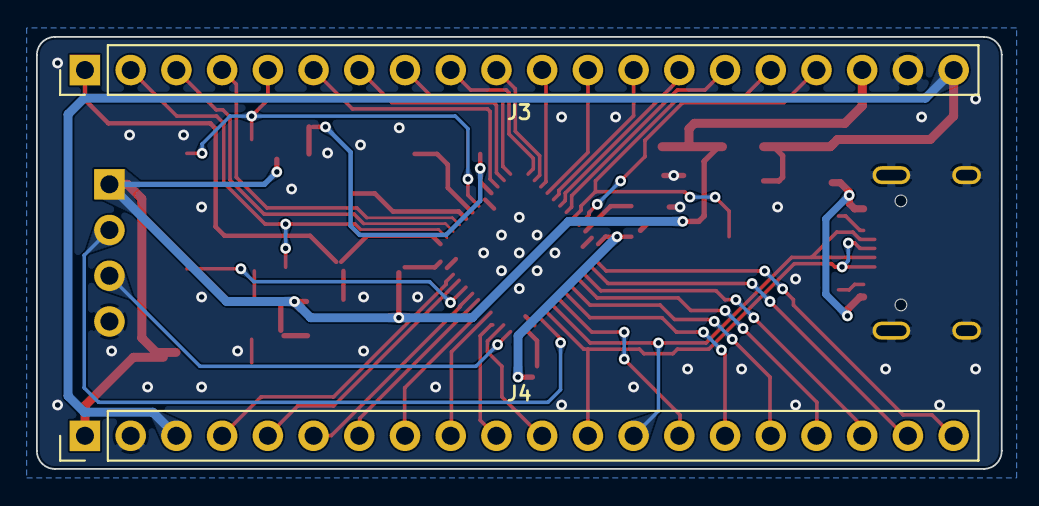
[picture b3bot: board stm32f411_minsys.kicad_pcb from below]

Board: 2 copper layers, 53.6 x 24.0 mm, 34 parts (2 on the bottom side), 49 nets.

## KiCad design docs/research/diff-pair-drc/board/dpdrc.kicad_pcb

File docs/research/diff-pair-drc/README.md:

# 实测：KiCad 10.0.8 的差分对 DRC（E1–E5）

票：[#44](https://github.com/immorcoding/PCB/issues/44)（地图 [#26](https://github.com/immorcoding/PCB/issues/26)）。日期 2026-11-26，KiCad 10.0.8，Windows 11。
分支 `research/diff-pair-drc`，只存档不合并。要核对的说法来自分支 `research/diff-pair-tooling` 的 `docs/research/diff-pair-tooling.md`（下称“调研”）第 3.4 节和第 9 节，那些都是读源码得出的，没有运行过。

## 怎么跑的

```
python docs/research/diff-pair-drc/run.py          # 在仓库根目录，系统 python
```

`run.py` 经 `core.heavy` 一次只跑一个重活：

1. `D:\KiCad\bin\python.exe docs/research/diff-pair-drc/make_board.py board templates/C-bga-065/C-bga-065.kicad_pro`：写夹具板 `board/dpdrc.kicad_pcb`（两层，线宽 0.1，对内中心距 0.25 即间隙 0.15，网络类 Default 只改了线宽、间距 0.1 和差分对参数）和 `board/predict.json`。坐标全部是整数 nm，直接写进 `VECTOR2I`；板文件里保留到 nm（例：`/E1B_N` 从 `7.911612 0.088389` 到 `12.911613 5.088389`）。
2. 每套规则一次：`kicad-cli pcb drc --severity-all --units mm --format json -o results/<套>.json work/<套>/dpdrc.kicad_pcb`，规则文件在 `rules/<套>.kicad_dru`。
3. `results/summary.txt`：每套规则里和差分对有关的报告原文，后面附 `predict.json` 的预测。

结束时没有 KiCad 进程在跑（`heavy.running()` 为空）。

同一套跑了两遍（第二遍只改了预测里圆弧耦合长度的算法），两遍的 94 个报告值逐个相同；报告的顺序和引用的是哪一段不同，因为 pcbnew 每次给对象新的 uuid。

预测是按调研第 3.4 节的读法算的：两段同层、方向向量整数叉积恰为 0、不共线、投影重叠，间隙在窗口内才算耦合；非耦合 = max(P 长, N 长) − Σ耦合重叠长度。**预测不含“两段之间没有别的铜”这一条**，所以 DRC 和预测不一样的地方就指向它。

每个用例是一对独立的网络 `/<用例>_P`、`/<用例>_N`，所有用例在同一块板上。读数的办法：`diff_pair_uncoupled (max 0.0001mm)`，没有报告即非耦合 ≤ 0.0001 mm，有报告就带实际值；`skew`、`length` 同样用极小的上限逼出实际值。

| 规则套 | 内容 |
|---|---|
| rs1_window_unc | `diff_pair_gap (min 0.14mm)(max 0.2mm)` + `diff_pair_uncoupled (max 0.0001mm)` |
| rs2_minonly_unc | `diff_pair_gap (min 0.14mm)`（无上限）+ `diff_pair_uncoupled (max 0.0001mm)` |
| rs3_window_only | 只有间隙窗口 |
| rs4_window_unc_loose | 间隙窗口 + `diff_pair_uncoupled (max 50mm)`（预算不会超） |
| rs5_skew_length | E3、E4 的 `skew (within_diff_pairs)` 和 `length` 探针 |

## 结果

### E1 整数偏移和“平行”的判定

| 用例 | 几何 | 调研的预测 | DRC（rs1、rs2） |
|---|---|---|---|
| E1A | 45°，N = P + 同一整数向量 | 耦合 | 耦合（无报告） |
| E1B | 45°，浮点中线、P/N 各端分别取整，两线方向差 (1, 0) nm | 非耦合 7.0711 | **耦合**（无报告） |
| E1C | 45°，N 末端故意偏 1 nm | 非耦合 7.0711 | **耦合** |
| E1D | 水平 10 mm，N 末端偏 1 nm | 非耦合 10 | **耦合** |
| E1G / E1H | 两个 45° 弯，按角平分线逐点取整 / 整数偏移线求交 | 0.2071 / 0.2071 | 0.2071 / 0.2071 |

调研说“叉积必须恰为 0”不成立。扫一遍偏差找门槛（N 末端横向偏 d，背离 P）：

| 组 | 长度 | 仍耦合的最大偏差 | 开始非耦合 |
|---|---|---|---|
| E1T 水平 | 10 mm | 1000 nm（1.0e-4 rad） | 3000 nm（3e-4 rad） |
| E1U 水平 | 1 mm | 100 nm（1.0e-4 rad） | 300 nm（3e-4 rad） |
| E1V 45° | 7.07 mm | x 偏 300 nm（垂直分量 3.0e-5 rad） | x 偏 1000 nm（1.0e-4 rad） |

门槛是**角度**，约 1e-4 rad（0.006°），和段长无关；正好 1e-4 时一例耦合一例不耦合。取整到 nm 带来的角度误差是 1 nm / 段长：0.1 mm 的段是 1e-5，离门槛差十倍。

E1G、E1H 的 0.2071 是两个 45° 弯的内外线长差：每个 45° 弯损失 S·tan 22.5°（中心距 S = 0.25 时 0.1036 mm）的耦合长度。

### E2 补偿凸起和圆弧

| 用例 | 几何（凸起都在 P 上，基线 10 mm） | 预测 rs1 / rs2 | DRC rs1 | DRC rs2 | 间隙报告（rs1、rs3、rs4） |
|---|---|---|---|---|---|
| E2Z | 直线对照 | 0 / 0 | 0 | 0 | 无 |
| E2A | 矩形向外，竖腿，高 0.3，顶 0.6 | 1.2 / 0.6 | 1.2000 | **1.2000** | **无** |
| E2B | 矩形向内，高 0.02（间隙 0.15→0.13） | 0.64 / 0.64 | 0.6400 | 0.6400 | 0.13 < 最小 0.14 |
| E2C | 梯形向外，45° 腿，高 0.3，顶 0.6 | 1.4485 / 0.8485 | 1.4485 | 0.8485 | 0.45 > 最大 0.2 |
| E2D | 圆角向外（`tune.py` 的形状：r 0.1 四分之一圆弧、腿 0.1、直顶 0.6） | 1.4283 / 0.8283 | 1.4283 | 0.8283 | 0.45 > 最大 0.2 |
| E2E | 半圆向外，r 0.3 | 0.9425 / 0.9425 | 0.9425 | 0.9425 | 无 |
| E2F | 90° 转弯，同心圆弧 r 1.125 / 0.875 | 0.3927 / 0.3927（耦合长度按内弧，见下） | 0.3927 | 0.3927 | 无 |
| E2G | 90° 转弯，P 圆弧、N 两段 45° 倒角 | 1.7671 | 1.7671 | 1.7671 | 无 |

- 顶边是直线、和 N 平行的向外凸起（梯形、圆角）：顶边**算耦合**，间隙 0.45。有间隙上限时报 `diff_pair_gap_out_of_range` 并计入非耦合；没有上限时它算耦合，非耦合反而少。
- 矩形竖腿凸起（E2A）：顶边**根本不算耦合**，有没有上限都一样，也不报间隙。原因见 E5：挡住它的是 P 自己在凸起起点处的基线。
- 向内凸起（E2B）：顶边耦合，间隙变小，低于下限就报错。
- 圆弧只和同心圆弧配对（E2F 耦合，耦合长度按内弧算，非耦合 = 外弧 − 内弧 = θ·S）；圆弧和直线不配对（E2G 整段弧都算非耦合）；半圆凸起（E2E）不报间隙，代价是整段弧长。

### E3 pad-to-die 和焊盘内的折线（rs5）

| 用例 | 几何 | DRC 的 P 长 | DRC 的 skew（N 对 P） |
|---|---|---|---|
| E3A | 两根直线 10 mm，P 起点焊盘 `die_length` 1.0 | 11.0000 | −1.0000 |
| E3B | P 在 0.6 mm 焊盘里折一下：(0,0)→(0.25,−0.25)→(0.5,0)→(10,0)，几何 10.2071 | **10.1434** | −0.1434 |
| E3C | 同样的折线，焊盘 0.3 mm，拐点在盘外 | 10.2071 | −0.2071 |

pad-to-die 计入 `length` 和 `skew`；焊盘里的那段按“中心到出盘点的直线”折算（E3B：中心到 (0.3, −0.2) 0.3606 + 0.2828 + 9.5 = 10.1434），和调研第 3.2 节、K53 一致。

### E4 `skew (within_diff_pairs)` 只命中一根网络（rs5）

| 用例 | 规则条件 | 长度（`length` 探针） | skew 报告 |
|---|---|---|---|
| E4A | `A.NetName == '/E4A_P'` | P 10.0000，N 11.0000 | **无**（静默跳过） |
| E4B | `A.inDiffPair('/E4B')`（对照） | 同上 | −1.0000 |
| E4C | 只有 `/E4C_P`，板上没有 `/E4C_N` | P 10.0000 | 无 |

### E5 成对换层、两线之间的铜

| 用例 | 几何 | 预测 | DRC rs1 | DRC rs2 |
|---|---|---|---|---|
| E5A | F 层成对线 45° 张开到过孔对（中心距 0.7），B 层收回；两个 GND 过孔在外侧 | 0.6364 | 0.6364 | 0.6364 |
| E5D | 宽对（间隙 0.75），中间无过孔（对照） | — / 0 | 10（间隙越界） | 0 |
| E5C | 宽对，GND 过孔在两线中间 x = 5 | — / 0 | 10 | **0** |
| E5E / E5F | 宽对，GND 过孔在 x = 0.3 / 9.7（过孔不压到端点） | — / 0 | 10 | **0** |
| E5G | 宽对，GND 过孔圆心在 x = 0（重叠段起点） | — / 0 | 10 | **10.0000** |
| E5H | 宽对，GND 过孔圆心在 x = 10（重叠段终点） | — / 0 | 10 | **0** |

- 过孔不计长度；张开段不平行，全算非耦合（E5A 正好是两段张开线 2 × 0.3182）；不同层上碰巧平行的两段不配对。
- “两段之间有没有别的铜”只在**重叠段的一端**查一条横线（这里是起点 x = 0）：中间、靠近两端但不压线的过孔都不挡；压在起点的过孔让整段 10 mm 不算耦合。E2A 的矩形凸起就是这样被 P 自己的基线挡掉的。两根线方向相反时查哪一端，没有测。

### 报告规则（rs3、rs4 对 rs1）

- 间隙越界**总是报**：rs3（无非耦合规则）和 rs4（非耦合预算 50 mm 没超）都报同样的 8 条。调研第 3.4 节“同时写两条规则、预算没超就不报间隙”不成立。
- 非耦合也超限时（rs1、rs2），每条间隙越界在报告里**出现两次**（rs1 共 16 条 = 2 × 8）。

## 对调研的更正

1. 第 0 节第 3 条、第 3.4 节“必须恰为 0”：实际门槛是约 1e-4 rad 的角度，不需要整数精确平行。
2. 第 3.4 节“判定”最后一条：间隙越界不受非耦合预算影响，总是报。
3. 第 3.4 节“补偿凸起”：向外凸起的顶边是否被挡，取决于重叠段起点那条横线上有没有铜；矩形竖腿被挡（不算耦合、不报间隙），梯形和圆角不被挡（算耦合，有上限就报间隙越界）。
4. 其余说法实测成立：只认同心圆弧、圆弧和直线不配对、过孔不计入非耦合的总长、不同层不配对、pad-to-die 计入、焊盘内折线折算、`within_diff_pairs` 只命中一根时静默跳过。

## 对差分对工具的直接含义（交给“定差分对工具的接口、指标和基准”那张票）

1. 几何不用整数精确构造：每个顶点各自取整到 nm 即可，只要段长 ≥ 0.1 mm（角度误差 ≤ 1e-5，门槛的十分之一）。工具自查可以卡“P/N 对应段方向差 < 1e-5 rad”。
2. 非耦合预算可以在构建时算准：本篇的预测模型（同层、平行、投影重叠、间隙窗口）加上“重叠段起点横线上无他铜”，在全部用例上和 DRC 一致到 0.0001 mm。每个 45° 弯花 S·tan 22.5°，同心圆弧转弯花 θ·S，成对换层花全部张开段。
3. 补偿凸起和 `diff_pair_gap` 的上限冲突：有上限时，顶边是直线的向外凸起（包括 `tune.py` 现在的圆角形状）一律报间隙越界，而且不论预算。可选的路：规则里不写间隙上限、只靠非耦合预算和工具自查；或者凸起只用圆弧（半圆）；矩形竖腿能躲开但靠的是上面那个只查一端的细节，不稳。由那张票定。
4. 凸起只向外：向内凸起使间隙变小，低于下限就报错。
5. `skew (within_diff_pairs)` 的条件只命中一根时不报任何东西：规则生成器要自查每对的两根都被同一条规则命中（`rules.dru_match` 一类的检查），不能靠 DRC 发现。
6. 对内偏差的长度口径和调研第 3.2 节相同（pad-to-die 计入、焊盘内折线折算），工具的长度要按这个算，或者像 K53 那样把拐点放到盘外。

## 文件

- `make_board.py`：夹具板和预测（KiCad 的 python）。
- `run.py`：构建、五套 DRC、汇总（系统 python，经 `core.heavy`）。
- `board/`：生成的板、工程文件、`predict.json`。
- `rules/`：五套规则文件。
- `results/`：五份 DRC 的 JSON 原文和 `summary.txt`。

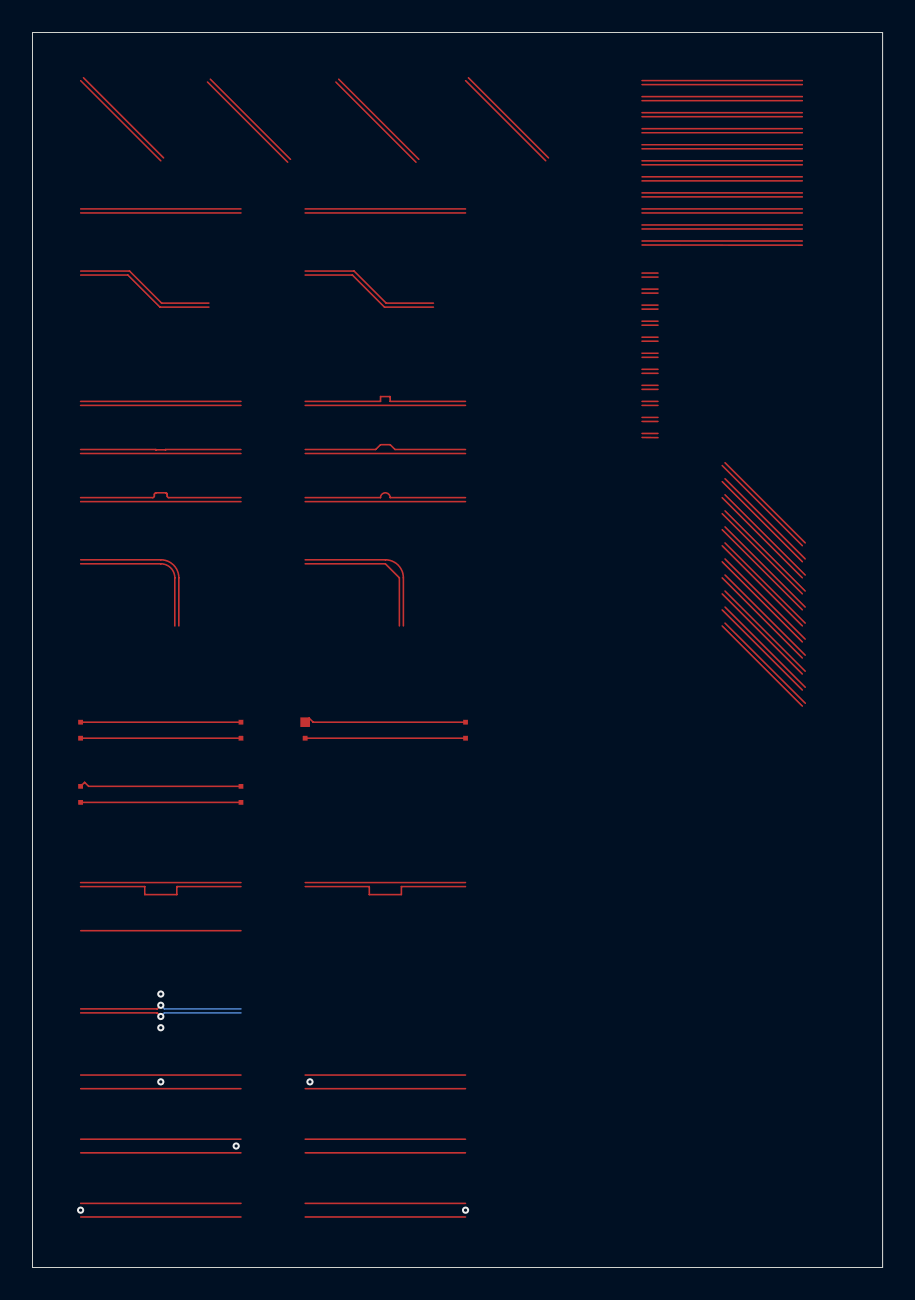
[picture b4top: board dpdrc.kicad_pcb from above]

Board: 2 copper layers, 53.0 x 77.0 mm, 6 parts (0 on the bottom side), 6 nets.

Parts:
AE3A: AE3A
AE3B: AE3B
AE3C: AE3C
BE3A: BE3A
BE3B: BE3B
BE3C: BE3C

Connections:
/E3A_N: AE3A.2, BE3A.2
/E3A_P: AE3A.1, BE3A.1
/E3B_N: AE3B.2, BE3B.2
/E3B_P: AE3B.1, BE3B.1
/E3C_N: AE3C.2, BE3C.2
/E3C_P: AE3C.1, BE3C.1
